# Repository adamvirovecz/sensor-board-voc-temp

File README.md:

# VOC, Humidity and Temperature Sensor Board
The board includes two sensors from Sensiron:
- **SGP41-D-R4** VOC and NOx sensor,
- **SHT41** temperature and humidity sensor.
The sensor data is accessible via UART interface. The voltage level is 5V, but the input is 3.3V compatible. A TXU0202 level shifter is used.
The sensor board is intended to be used with other Sensiron sensors (like SPS30 and SFA30). The 5V interface was chosen so that a central controller can use the same interface type to connect to any of the sensors.
## Image of the assembled board
TODO
## Repository structure
- bom: interactive bom and csv
- gerbers: manufacturing files
- pdf: pdf output of schematic

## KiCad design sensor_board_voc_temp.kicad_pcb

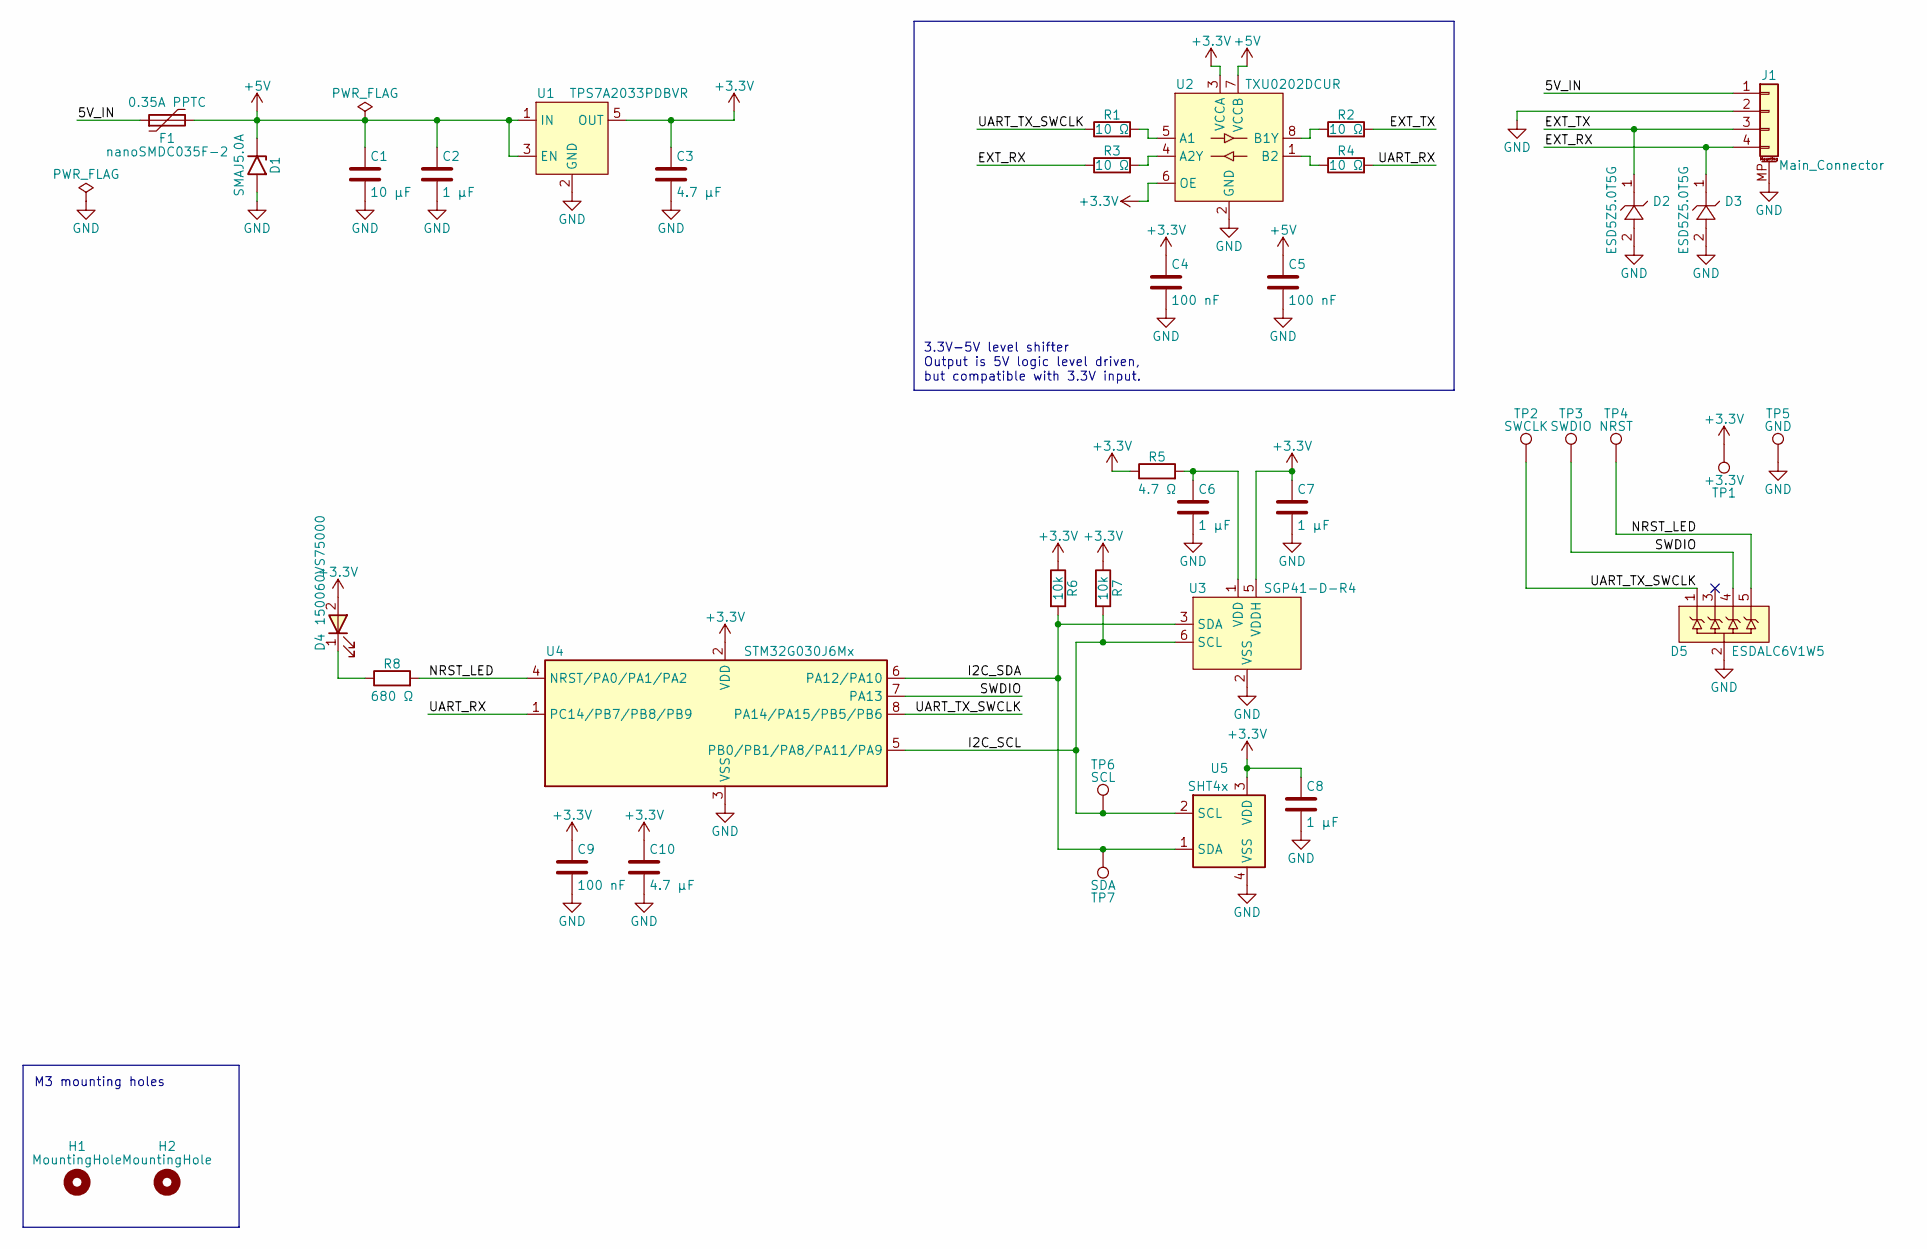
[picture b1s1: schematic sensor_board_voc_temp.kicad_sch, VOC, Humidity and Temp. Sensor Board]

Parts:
C1: 10 µF; C_0805_2012Metric; MPN 0805YC106KAT2A
C2, C6, C7, C8: 1 µF; C_0603_1608Metric; MPN C1608X7R1C105K080AC
C3, C10: 4.7 µF; C_0805_2012Metric; MPN GRM21BR71C475KE51K
C4, C5, C9: 100 nF; C_0603_1608Metric; MPN 0603YC104KAT2A
D1: SMAJ5.0A; D_SMA; MPN SMAJ5.0A
D2, D3: ESD5Z5.0T5G; D_SOD-523; MPN ESD5Z5.0T5G
D4: 150060VS75000; LED_0603_1608Metric; MPN 150060VS75000
D5: ESDALC6V1W5; SOT-353_SC-70-5; MPN ESDALC6V1W5
F1: 0.35A PPTC; Fuse_LittelFuse_nanoSMDC_Series; MPN nanoSMDC035F-2
H1, H2: MountingHole; MountingHole_3.2mm_M3_ISO7380
J1: Main_Connector; Molex_CLIK_Mate_213226_0410_1x04_1MP_P1.50mm_Horizontal; MPN 213226-0410
R1, R2, R3, R4: 10 Ω; R_0603_1608Metric; MPN CRCW060310R0FKEAHP
R5: 4.7 Ω; R_0603_1608Metric; MPN CRCW06034R70FKEA
R6, R7: 10k; R_0603_1608Metric; MPN CRCW060310K0FKECC
R8: 680 Ω; R_0603_1608Metric; MPN CRCW0603680RFKEA
TP1: +3.3V; TestPoint_Pad_D1.5mm
TP2: SWCLK; TestPoint_Pad_D1.5mm
TP3: SWDIO; TestPoint_Pad_D1.5mm
TP4: NRST; TestPoint_Pad_D1.5mm
TP5: GND; TestPoint_Pad_D1.5mm
TP6: SCL; TestPoint_Pad_D1.5mm
TP7: SDA; TestPoint_Pad_D1.5mm
U1: TPS7A2033PDBVR; SOT-23-5; MPN TPS7A2033PDBVR
U2: TXU0202DCUR; VSSOP-8_2.3x2mm_P0.5mm; MPN TXU0202DCUR
U3: SGP41-D-R4; DFN-6-1EP_2.44x2.44mm_P0.8mm_EP1.25x1.64mm; MPN SGP41-D-R4
U4: STM32G030J6Mx; SOIC-8_3.9x4.9mm_P1.27mm; MPN STM32G030J6M6
U5: SHT4x; Sensirion_DFN-4_1.5x1.5mm_P0.8mm_SHT4x_NoCentralPad; MPN SHT41-AD1F-R2

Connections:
+3.3V: C3.1, C4.1, C7.1, C8.1, C9.1, C10.1, D4.2 (A), R5.1, R6.1, R7.1, TP1.1, U1.5 (OUT), U2.3 (VCCA), U2.6 (OE), U3.5 (VDDH), U4.2 (VDD), U5.3 (VDD)
+5V: C1.1, C2.1, C5.1, D1.1 (A1), F1.2, U1.1 (IN), U1.3 (EN), U2.7 (VCCB)
/5V_IN: F1.1, J1.1
/EXT_RX: D3.1, J1.4, R3.1
/EXT_TX: D2.1, J1.3, R2.2
/I2C_SCL: R7.2, TP6.1, U3.6 (SCL), U4.5 (PB0/PB1/PA8/PA11/PA9), U5.2 (SCL)
/I2C_SDA: R6.2, TP7.1, U3.3 (SDA), U4.6 (PA12/PA10), U5.1 (SDA)
/NRST_LED: D5.5, R8.2, TP4.1, U4.4 (NRST/PA0/PA1/PA2)
/SWDIO: D5.4, TP3.1, U4.7 (PA13)
/UART_RX: R4.2, U4.1 (PC14/PB7/PB8/PB9)
/UART_TX_SWCLK: D5.1, R1.1, TP2.1, U4.8 (PA14/PA15/PB5/PB6)
GND: C1.2, C2.2, C3.2, C4.2, C5.2, C6.2, C7.2, C8.2, C9.2, C10.2, D1.2 (A2), D2.2, D3.2, D5.2, J1.2, J1.MP (MountPin), TP5.1, U1.2 (GND), U2.2 (GND), U3.2 (VSS), U3.4 (N/A), U3.EP, U4.3 (VSS), U5.4 (VSS)
unnamed: D4.1 (K), R8.1
unnamed: R1.2, U2.5 (A1)
unnamed: R3.2, U2.4 (A2Y)
unnamed: R2.1, U2.8 (B1Y)
unnamed: R4.1, U2.1 (B2)
unnamed: C6.1, R5.2, U3.1 (VDD)

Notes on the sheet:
M3 mounting holes
3.3V-5V level shifter Output is 5V logic level driven, but compatible with 3.3V input.

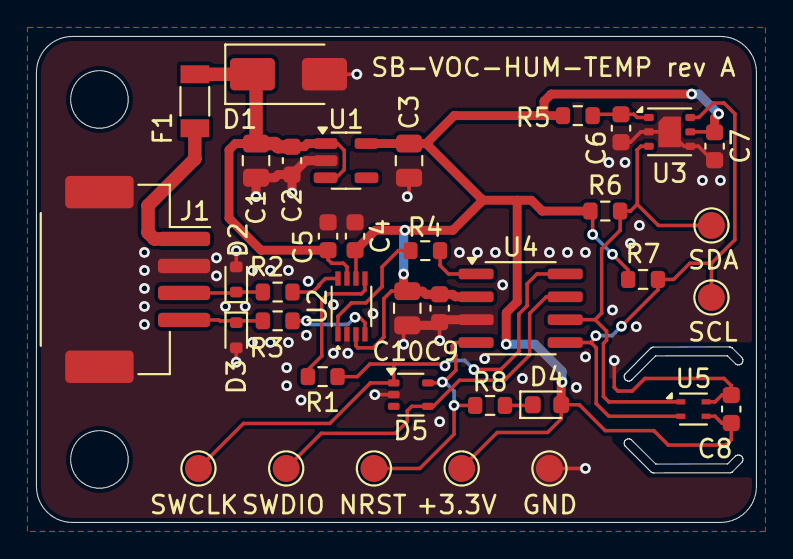
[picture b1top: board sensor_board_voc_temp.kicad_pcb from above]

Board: 2 copper layers, 40.0 x 27.0 mm, 39 parts (0 on the bottom side), 18 nets.

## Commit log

2024-10-06 Initial commit. Rev A board design.
2024-10-06 Create LICENSE
